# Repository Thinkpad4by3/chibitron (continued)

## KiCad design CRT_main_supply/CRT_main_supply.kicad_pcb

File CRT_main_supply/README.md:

## CRT HV Supply Gen.1 V1

## Status
- Completed, succeeded by CRT_main_supply_2
- I would not recommend building this supply

##  Design & Architecture 
Uses the LM5180 Primary Side Regulated flyback controller. This was the easiest control to implement, given the original prototype was based on the LT8304-1 controller, which is the Analog Design variant of the same IC. The following reference design was used as my starting point for an inital prototype made a few months prior. This proved to be enough to get some life into a 3BP1, so I continued forward with that. I used the same 0399-T208 transformer, rated for 1KV output at up to 15mA, which was great for availability when I started this project. 

The use of a PSR regulator was great since it eliminated the need for any output sense such as a TL431 or large resistor ladder, and made it quite easy to slap a few of them on for the A2, Filament & Grid drive all with one converter. The supply was biased such that the ground reference could be moved around as needed, for experimentation purposes. 

Focus and Brightness are controlled through resistor dividers between A2 and Cathode.

Otherwise, the overall design was quite simple, and would be further revised later. 

Link: https://www.analog.com/en/resources/technical-articles/1000-v-output-no-opto-isolated-flyback-converter.html

## Troubleshooting & Bring-up 
Main problem with bring-up on this was down to the LM5180's undiagnosed requirement for RC filtering on the primary side. Due to the large step-up ratio and leakage inductance within the transformer, ringing under load would go far above the >85V rating of the internal FET. This is less of a problem when used in a 1:1 or lower ratio, where the reflected voltage is more...reasonable. A 220p + 100 ohm resistor as suggested by the LT8304 ended up being a good solution to fix this ringing, however not before nuking about 10 of those LM5180s. Atleast they're more reasonably priced than the LT8304. 

Other major issue was that the Filament was tied to the -1500V rail instead of floating off the cathode. For the purposes of most tubes, this is not a problem. Most CRTs have a H-H-K arrangement, which means the cathode is indirectly heated, and can generally float within +/- 125V of the cathode. G1-cutoff should be no more than 100V from the cathode, so this is generally fine. However, on some tubes, they are tied H-HK where either the tube is directly heated and the cathode is the heater, or the tube has the two connections internally tied to save pin-count. Either way, given the goal of maximum compatibility, mandating a tied HK was necessary.

Supply was able to light up a 3BP1, at this point I did not have many tubes to test with and this was the only tube I felt safe to test with. It did provide a decent picture, albeit a bit fuzzy. Some of this was due to unfiltered switching noise from the HV supplies. At this point, it just lit up with a dot since deflection_amp has not been brought up yet. It was however, good enough to get through deflection_amp developed, and therefore served its purpose.

## Learnings
LM5180 has some issues, regulation isn't wonderful and didn't like starting up the main filament supplies. Filament took nearly 6 seconds to get to full voltage, and another 10 seconds for the tube to start conducting. 

Ground reference can be set to GND -> A2 is optimal.

H-HK filament biasing required.

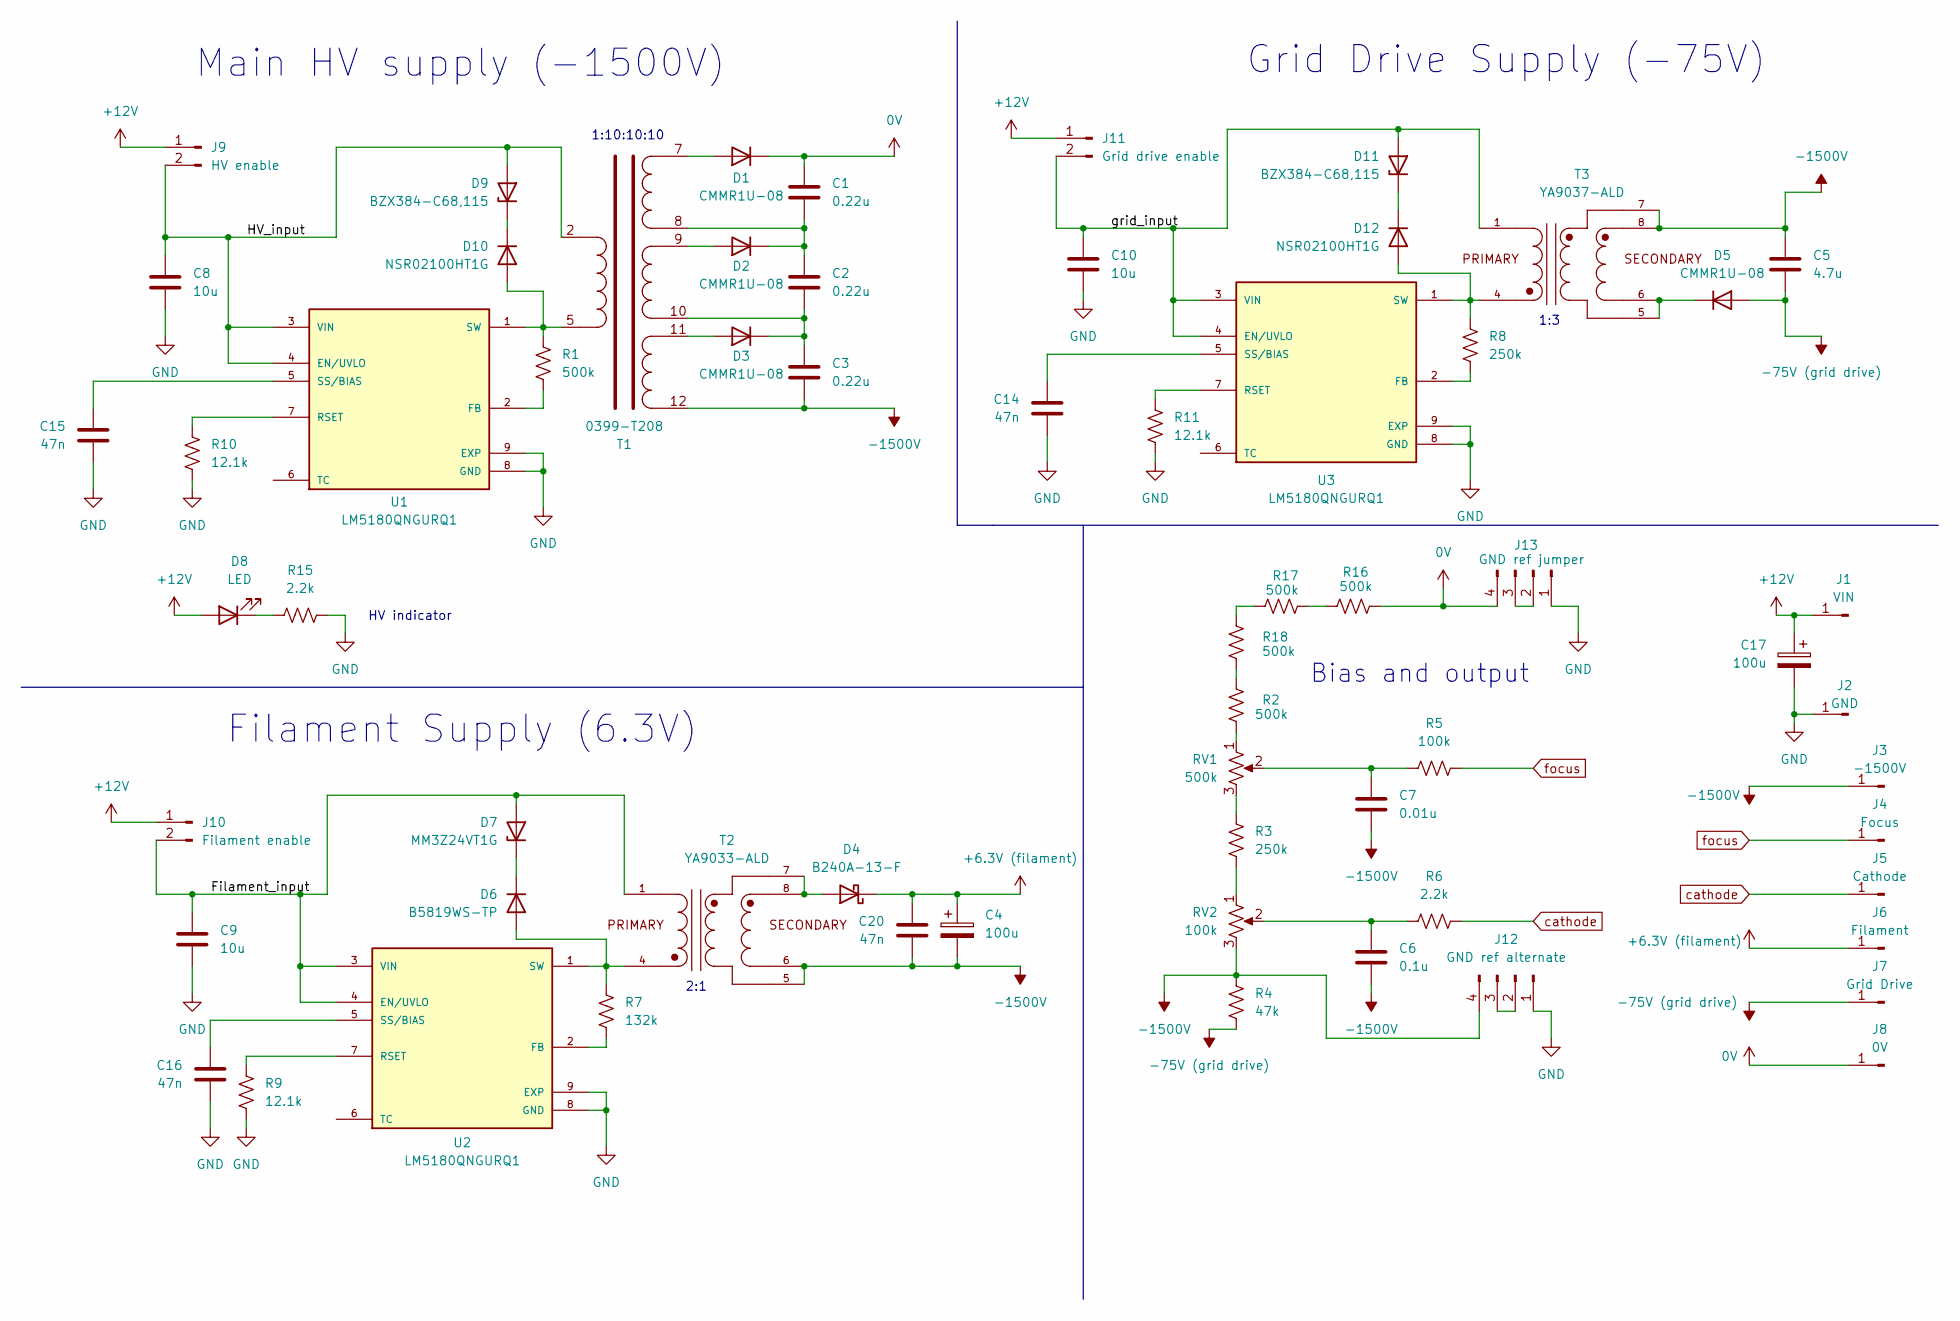
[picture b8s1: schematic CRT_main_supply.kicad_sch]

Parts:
C1, C2, C3: 0.22u; C_1812_4532Metric_Pad1.57x3.40mm_HandSolder
C4, C17: 100u; C_Elec_6.3x5.8
C5: 4.7u; C_1206_3216Metric_Pad1.33x1.80mm_HandSolder
C6: 0.1u; C_0603_1608Metric_Pad1.08x0.95mm_HandSolder
C7: 0.01u; C_1206_3216Metric_Pad1.33x1.80mm_HandSolder
C8, C9, C10: 10u; C_1210_3225Metric_Pad1.33x2.70mm_HandSolder
C14, C15, C16, C20: 47n; C_0603_1608Metric_Pad1.08x0.95mm_HandSolder
D1, D2, D3, D5: CMMR1U-08; D_SOD-123F
D4: B240A-13-F; D_SMA_Handsoldering
D6: B5819WS-TP; D_SOD-323_HandSoldering
D7: MM3Z24VT1G; D_SOD-323_HandSoldering
D8: LED; LED_0805_2012Metric
D9, D11: BZX384-C68,115; D_SOD-323_HandSoldering
D10, D12: NSR02100HT1G; D_SOD-323_HandSoldering
J1: VIN; PinSocket_1x01_P2.54mm_Vertical
J2: GND; PinSocket_1x01_P2.54mm_Vertical
J3: -1500V; PinSocket_1x01_P2.54mm_Vertical
J4: Focus; PinSocket_1x01_P2.54mm_Vertical
J5: Cathode; PinSocket_1x01_P2.54mm_Vertical
J6: Filament; PinSocket_1x01_P2.54mm_Vertical
J7: Grid Drive; PinSocket_1x01_P2.54mm_Vertical
J8: 0V; PinSocket_1x01_P2.54mm_Vertical
J9: HV enable; PinHeader_1x02_P2.54mm_Vertical
J10: Filament enable; PinHeader_1x02_P2.54mm_Vertical
J11: Grid drive enable; PinHeader_1x02_P2.54mm_Vertical
J12: GND ref alternate; PinSocket_1x04_P2.54mm_Vertical
J13: GND ref jumper; PinSocket_1x04_P2.54mm_Vertical
R1: 500k; R_0805_2012Metric_Pad1.20x1.40mm_HandSolder
R2, R16, R17, R18: 500k; R_1206_3216Metric_Pad1.30x1.75mm_HandSolder
R3, R8: 250k; R_1206_3216Metric_Pad1.30x1.75mm_HandSolder
R4: 47k; R_1206_3216Metric_Pad1.30x1.75mm_HandSolder
R5: 100k; R_1206_3216Metric_Pad1.30x1.75mm_HandSolder
R6, R15: 2.2k; R_0805_2012Metric_Pad1.20x1.40mm_HandSolder
R7: 132k; R_0603_1608Metric_Pad0.98x0.95mm_HandSolder
R9, R10, R11: 12.1k; R_0603_1608Metric_Pad0.98x0.95mm_HandSolder
RV1: 500k; Potentiometer_Bourns_3296W_Vertical
RV2: 100k; Potentiometer_Bourns_3296W_Vertical
T1: 0399-T208
T2: YA9033-ALD; XFMR_YA9033-ALD; PARTREV 05/12/21
T3: YA9037-ALD; XFMR_YA9033-ALD; PARTREV 05/12/21
U1, U2, U3: LM5180QNGURQ1; SON80P400X400X80-9N; PARTREV A

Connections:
0V: C1.1, D1.1 (K), J8.1, J13.4, R16.2
+6.3V (filament): C4.1, C20.1, D4.1 (K), J6.1
+12V: C17.1, D8.2 (A), J1.1, J9.1, J10.1, J11.1
-75V (grid drive): C5.2, D5.2 (A), J7.1, R4.2
-1500V: C3.2, C4.2, C5.1, C6.2, C7.2, C20.2, J3.1, J12.4, R4.1, RV2.3, T1.12, T2.5, T2.6, T3.7, T3.8
/Filament_input: C9.1, D7.2 (A), J10.2, T2.1, U2.3 (VIN), U2.4 (EN/UVLO)
/HV_input: C8.1, D9.2 (A), J9.2, T1.2, U1.3 (VIN), U1.4 (EN/UVLO)
/grid_input: C10.1, D11.2 (A), J11.2, T3.1, U3.3 (VIN), U3.4 (EN/UVLO)
GND: C8.2, C9.2, C10.2, C14.2, C15.2, C16.2, C17.2, J2.1, J12.1, J13.1, R9.2, R10.2, R11.2, R15.2, U1.8 (GND), U1.9 (EXP), U2.8 (GND), U2.9 (EXP), U3.8 (GND), U3.9 (EXP)
unnamed: C6.1, R6.1, RV2.2
unnamed: C7.1, R5.1, RV1.2
unnamed: D1.2 (A), T1.7
unnamed: D2.2 (A), T1.9
unnamed: C1.2, C2.1, D2.1 (K), T1.8
unnamed: D3.2 (A), T1.11
unnamed: C2.2, C3.1, D3.1 (K), T1.10
unnamed: D4.2 (A), T2.7, T2.8
unnamed: D5.1 (K), T3.5, T3.6
unnamed: D6.2 (A), R7.1, T2.4, U2.1 (SW)
unnamed: D6.1 (K), D7.1 (K)
unnamed: D8.1 (K), R15.1
unnamed: D10.2 (A), R1.1, T1.5, U1.1 (SW)
unnamed: D9.1 (K), D10.1 (K)
unnamed: D11.1 (K), D12.1 (K)
unnamed: D12.2 (A), R8.1, T3.4, U3.1 (SW)
unnamed: J12.2, J12.3
unnamed: J13.2, J13.3
unnamed: R2.2, RV1.1
unnamed: R3.1, RV1.3
unnamed: R3.2, RV2.1
unnamed: R16.1, R17.2
unnamed: R17.1, R18.1
unnamed: R2.1, R18.2
unnamed: R1.2, U1.2 (FB)
unnamed: R10.1, U1.7 (RSET)
unnamed: C15.1, U1.5 (SS/BIAS)
unnamed: R7.2, U2.2 (FB)
unnamed: R9.1, U2.7 (RSET)
unnamed: C16.1, U2.5 (SS/BIAS)
unnamed: R8.2, U3.2 (FB)
unnamed: R11.1, U3.7 (RSET)
unnamed: C14.1, U3.5 (SS/BIAS)
cathode: J5.1, R6.2
focus: J4.1, R5.2

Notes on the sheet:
1:3
HV indicator
1:10:10:10
Filament Supply (6.3V)
Bias and output
Main HV supply (-1500V)
Grid Drive Supply (-75V)
2:1

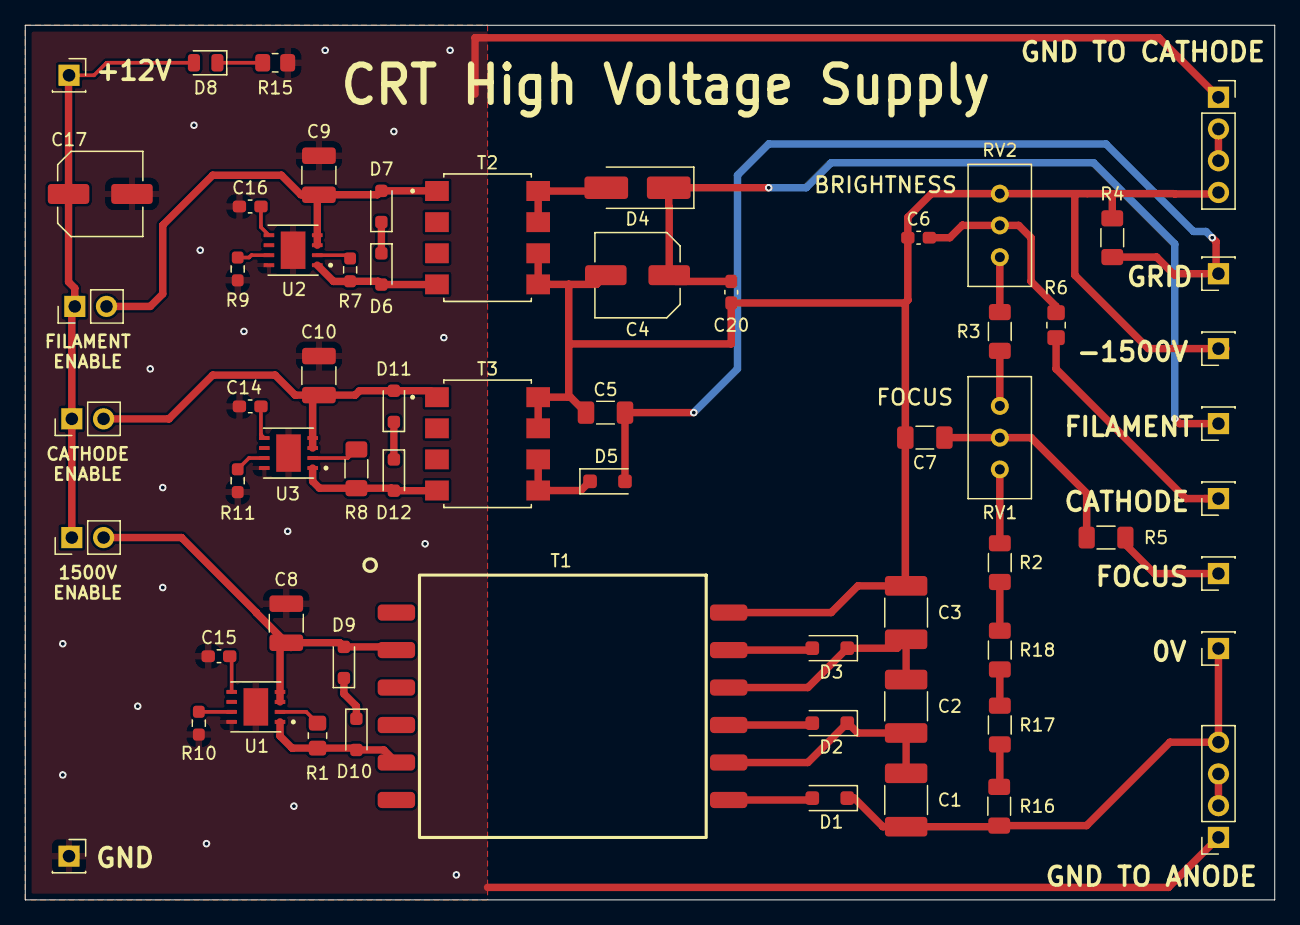
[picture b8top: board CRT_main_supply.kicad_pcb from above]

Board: 2 copper layers, 100.0 x 70.0 mm, 63 parts (0 on the bottom side), 44 nets.

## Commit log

2025-04-16 initial upload of deflection amp 3
2025-04-16 add pdf
2025-04-17 fixed BOM + DAC footprint
2025-04-17 fixed BOM + DAC footprint + regenerated files
2025-04-17 cleanup
2025-04-17 cleanup part 2
2025-04-17 cleanup part 3
2025-05-18 main supply old
2025-05-18 defl board upload
2025-12-11 add main supply 3
2026-02-02 defl 5 + mainboard 3
2026-02-02 add new folders
2026-02-02 change readmes
2026-02-02 readme
2026-02-02 readme 2
2026-02-02 readme 3
2026-02-02 readme 4
2026-02-02 readme 5
2026-02-02 readme 6
2026-02-02 readme erformat
2026-02-02 readme reformat 2
2026-02-13 more updates
2026-02-14 add VM
2026-02-14 rename
2026-02-17 finished routing and layout
    need to update U6 stuff
2026-02-17 add PDF out
2026-02-17 redo PDF
2026-02-18 testload
2026-03-17 added defl amp 6
